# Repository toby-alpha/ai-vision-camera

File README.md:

# ai-vision-camera
A CM5 Based Camera used for Scene Description

**As mentioned in the bottom of this ReadMe, JLCCNC  generously sponsored my project, making it possible for me, as a high school student, to create a professional-grade end product. I would truely recommend that you take a look at the services JLCCNC can provide, the photos really show the quality for itself.**

## What is this?

A Radxa CM5 driven camera, capable of providing detailed scene description by taking in an image through a camera and outputing it as sound, through a speaker,  to a visually impared person by using an on-board AI alogrithm. It's then housed in a 6061 Aluminium Case, providing both elegance but also an efficient method of heat disipation. 

## CAD

## PCB(s)

### Main Radxa CM5 Interface

### WS2812B RGB Halo

### Trigger Button

## Wiring Diagram

## Why I made this?

So.. I really wanted to explore using a local AI alogrithm, that could be effectivly tuned to meet a purpose. Doing reaserch, I really loved the form factor, and power of the CM5, and thus wanted to combine the two together to produce something meaningful. To be meaningful, and fufil a real world purpose, the device takes in an image, then spits out a description through a speaker, to aid a visually impared person. I see this as both being a really effective way to explore and deepen my knowledge in this area, but also create a positive contribution to society. This concept of description can be seen in other solutions, such as Microsoft's SeeingAI. I think my project has been a really meaningful exploration of this technology.

## BOM

|Item                                |Cost AUD|Cost USD|Vendor    |Link                                                |
|------------------------------------|--------|--------|----------|----------------------------------------------------|
|Top Case                            |76      |49.4  |JLCCNC   |https://jlccnc.com/?from=Toby              |
|Bottom Case                         |76      |49.4    |JLCCNC   |https://jlccnc.com/?from=Toby               |
|LED Diffuser                        |20      |13      |JLCCNC   |https://jlccnc.com/?from=Toby               |
|Button                              |15      |9.75    |JLCCNC   |https://jlccnc.com/?from=Toby               |
|                                    |        |        |          |                                                    |
|Radxa CM5                           |137 (Will aquire personally, if this is too much)   |90     |Aliexpress|https://vi.aliexpress.com/item/1005007512045699.html|
|Radxa 8MP Camera                    |30      |19.5    |Aliexpress|https://vi.aliexpress.com/item/1005006991546297.html|
|Hot Air Gun (For the back connector)|46      |29.9    |Aliexpress|https://vi.aliexpress.com/item/1005008042972683.html|
|PCB Components                      |15      |9.75    |Aliexpress|Misc                                                |
|Misc (Bolts, Camera Cable, Speaker, Vibration Motor)          |15      |9.75    |Aliexpress|Misc                                                |
|                                    |        |        |          |                                                    |
|Main PCB                            |10      |6.5     |JLCPCB    |Manual Quote - Please Enquire to View               |
|Main PCBA                           |48      |31.2    |JLCPCB    |Manual Quote - Please Enquire to View               |
|LED Diffuser PCB                    |5       |3.25    |JLCPCB    |Manual Quote - Please Enquire to View               |
|Button PCB                          |5       |3.25    |JLCPCB    |Manual Quote - Please Enquire to View               |
|                                    |        |        |          |                                                    |
|Total                               |477     |311   |          |                                                    |

---

### A HUGE thank you so JLCCNC for sponsoring the CNC part of this project. Their assistance in machining will be crucial in helping this project come to life. 

If you are looking for CNC services, I can not reccomend them more. https://jlccnc.com/?from=Toby

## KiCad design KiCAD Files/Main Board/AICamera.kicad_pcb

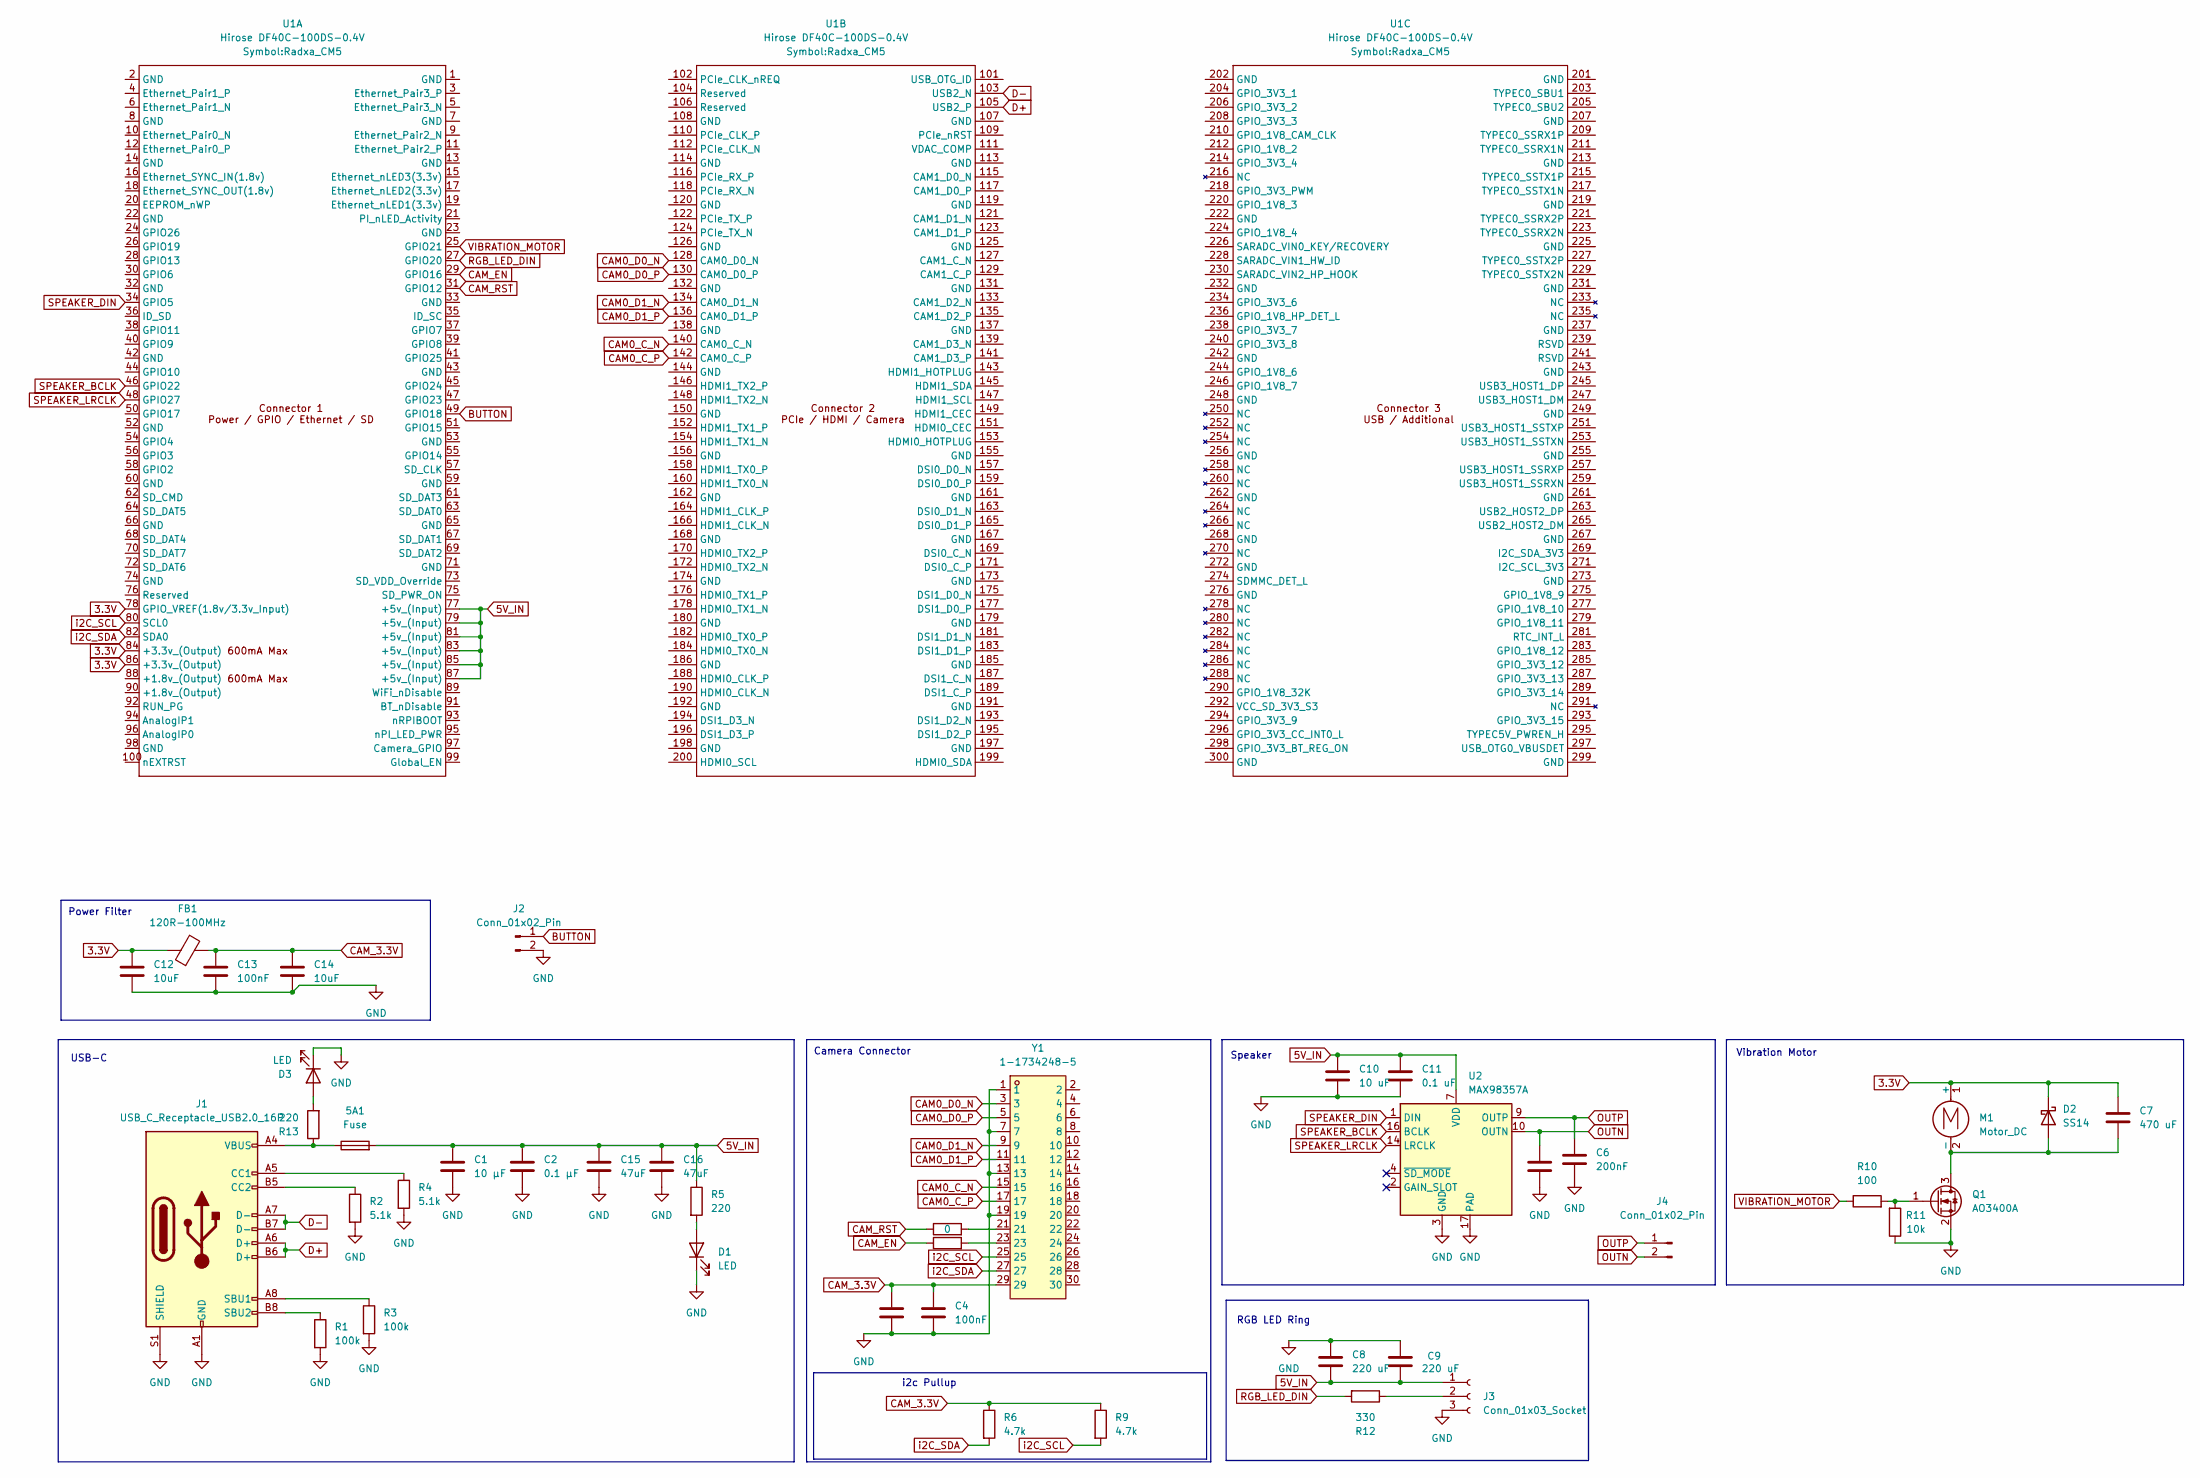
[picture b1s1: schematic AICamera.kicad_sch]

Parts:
5A1: Fuse; Fuse_1206_3216Metric
C1: 10 µF; C_0805_2012Metric
C2: 0.1 µF; C_0805_2012Metric
C3, C12, C14: 10uF; C_0805_2012Metric
C4, C13: 100nF; C_0805_2012Metric
C5, C6: 200nF; C_0805_2012Metric
C7: 470 uF; C_0805_2012Metric
C8, C9: 220 uF; C_0805_2012Metric
C10: 10 uF; C_0805_2012Metric
C11: 0.1 uF; C_0805_2012Metric
C15, C16: 47uF; C_1206_3216Metric
D1, D3: LED; LED_0805_2012Metric
D2: SS14; D_SMA
FB1: 120R-100MHz; C_0805_2012Metric
J1: USB_C_Receptacle_USB2.0_16P; USB_C_Receptacle_G-Switch_GT-USB-7010ASV
J2: Conn_01x02_Pin; TestPoint_Pad_3.0x3.0mm
J3: Conn_01x03_Socket; TestPoint_Pad_2.5x2.5mm
J4: Conn_01x02_Pin; TestPoint_Pad_2.0x2.0mm
M1: Motor_DC; TestPoint_Pad_2.0x2.0mm
Q1: AO3400A; SOT-23
R1, R3: 100k; R_0805_2012Metric
R2, R4: 5.1k; R_0805_2012Metric
R5, R13: 220; R_0805_2012Metric
R6, R9: 4.7k; R_0603_1608Metric
R7, R8: 0; R_0805_2012Metric
R10: 100; R_0805_2012Metric
R11: 10k; R_0805_2012Metric
R12: 330; R_0805_2012Metric
U1: Hirose DF40C-100DS-0.4V; Radxa_CM5
U2: MAX98357A; TQFN-16-1EP_3x3mm_P0.5mm_EP1.23x1.23mm
Y1: 1-1734248-5; CONN-SMD_1-1734248-5; LCSC Part C2922285

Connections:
3.3V: C7.2, C12.1, D2.1 (K), FB1.1, M1.1 (+), U1.78 (GPIO_VREF(1.8v/3.3v_Input)), U1.84 (+3.3v_(Output)), U1.86 (+3.3v_(Output))
5V_IN: 5A1.2, C1.1, C2.1, C8.2, C9.2, C10.1, C11.1, C15.1, C16.1, J3.1, R5.1, U1.77 (+5v_(Input)), U1.79 (+5v_(Input)), U1.81 (+5v_(Input)), U1.83 (+5v_(Input)), U1.85 (+5v_(Input)), U1.87 (+5v_(Input)), U2.7 (VDD), U2.8 (VDD)
BUTTON: J2.1, U1.49 (GPIO18)
CAM0_C_N: U1.140 (CAM0_C_N), Y1.15
CAM0_C_P: U1.142 (CAM0_C_P), Y1.17
CAM0_D0_N: U1.128 (CAM0_D0_N), Y1.3
CAM0_D0_P: U1.130 (CAM0_D0_P), Y1.5
CAM0_D1_N: U1.134 (CAM0_D1_N), Y1.9
CAM0_D1_P: U1.136 (CAM0_D1_P), Y1.11
CAM_3.3V: C3.1, C4.1, C13.1, C14.1, FB1.2, R6.1, R9.1, Y1.29
CAM_EN: R8.1, U1.29 (GPIO16)
CAM_RST: R7.1, U1.31 (GPIO12)
D+: J1.A6 (D+), J1.B6 (D+), U1.105 (USB2_P)
D-: J1.A7 (D-), J1.B7 (D-), U1.103 (USB2_N)
GND: C1.2, C2.2, C3.2, C4.2, C5.2, C6.2, C8.1, C9.1, C10.2, C11.2, C12.2, C13.2, C14.2, C15.2, C16.2, D1.1 (K), D3.1 (K), J1.A1 (GND), J1.A12 (GND), J1.B1 (GND), J1.B12 (GND), J1.S1 (SHIELD), J2.2, J3.3, Q1.2 (S), R1.2, R2.2, R3.2, R4.2, R11.1, U2.3 (GND), U2.11 (GND), U2.15 (GND), U2.17 (PAD), Y1.1, Y1.7, Y1.13, Y1.19
unnamed: 5A1.1, J1.A4 (VBUS), J1.A9 (VBUS), J1.B4 (VBUS), J1.B9 (VBUS), R13.1
unnamed: D1.2 (A), R5.2
unnamed: C7.1, D2.2 (A), M1.2 (-), Q1.3 (D)
unnamed: D3.2 (A), R13.2
unnamed: J1.A5 (CC1), R4.1
unnamed: J1.B5 (CC2), R2.1
unnamed: J1.A8 (SBU1), R3.1
unnamed: J1.B8 (SBU2), R1.1
unnamed: J3.2, R12.1
unnamed: Q1.1 (G), R10.2, R11.2
unnamed: R7.2, Y1.21
unnamed: R8.2, Y1.23
OUTN: C5.1, J4.2, U2.10 (OUTN)
OUTP: C6.1, J4.1, U2.9 (OUTP)
RGB_LED_DIN: R12.2, U1.27 (GPIO20)
SPEAKER_BCLK: U1.46 (GPIO22), U2.16 (BCLK)
SPEAKER_DIN: U1.34 (GPIO5), U2.1 (DIN)
SPEAKER_LRCLK: U1.48 (GPIO27), U2.14 (LRCLK)
VIBRATION_MOTOR: R10.1, U1.25 (GPIO21)
i2C_SCL: R9.2, U1.80 (SCL0), Y1.25
i2C_SDA: R6.2, U1.82 (SDA0), Y1.27

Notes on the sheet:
i2c Pullup
Speaker
USB-C
RGB LED Ring
Power Filter
Camera Connector
Vibration Motor

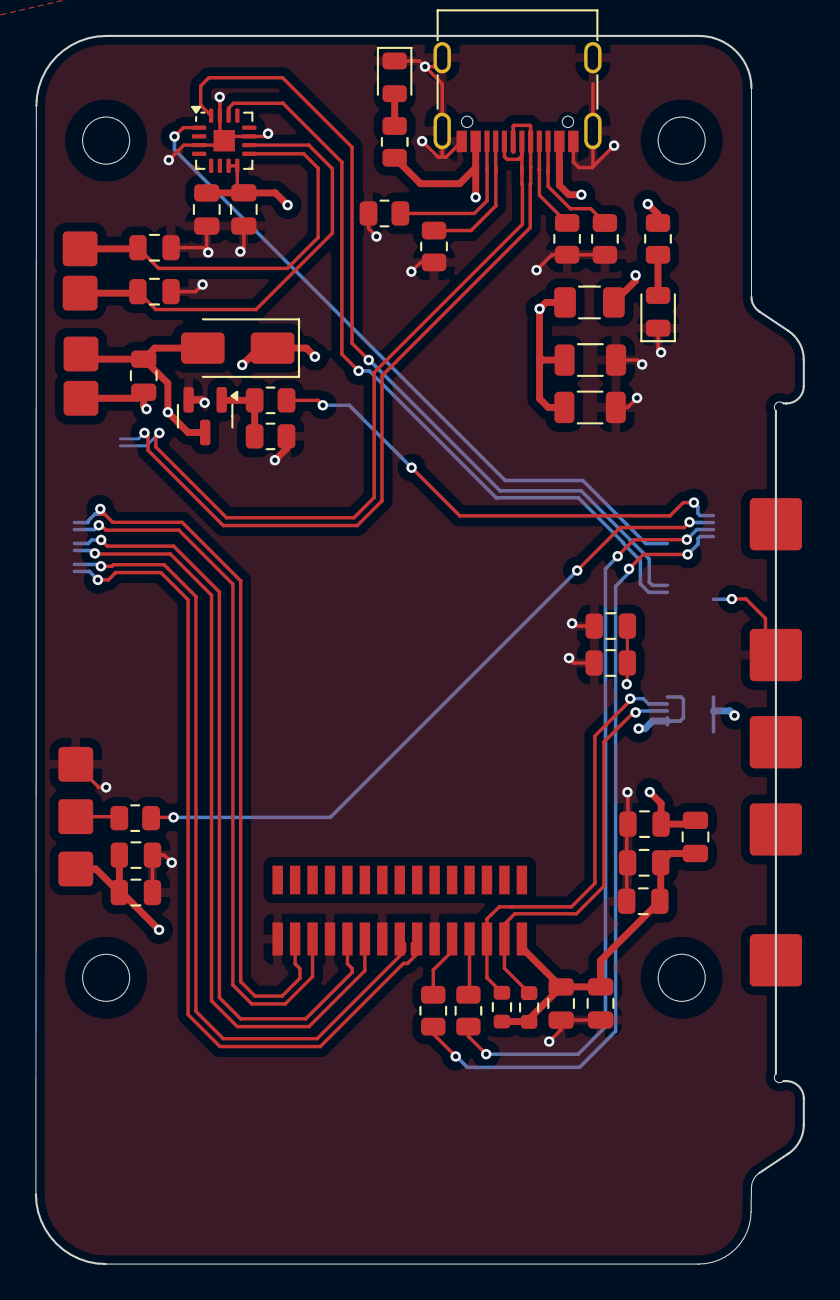
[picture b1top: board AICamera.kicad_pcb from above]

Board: 4 copper layers, 44.0 x 70.4 mm, 43 parts (1 on the bottom side), 36 nets.

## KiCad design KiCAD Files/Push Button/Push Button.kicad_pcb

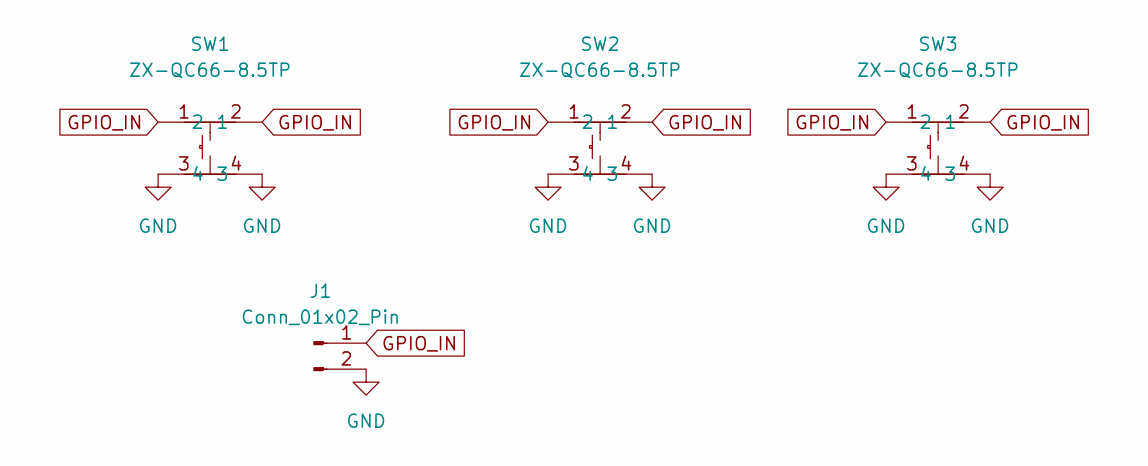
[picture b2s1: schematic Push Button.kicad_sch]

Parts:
J1: Conn_01x02_Pin; TestPoint_Pad_3.0x3.0mm
SW1, SW2, SW3: ZX-QC66-8.5TP; KEY-SMD_4P-L6.0-W6.0-P4.50-LS8.6_H8.5; LCSC Part C7470159

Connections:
GND: J1.2, SW1.3, SW1.4, SW2.3, SW2.4, SW3.3, SW3.4
GPIO_IN: J1.1, SW1.1, SW1.2, SW2.1, SW2.2, SW3.1, SW3.2

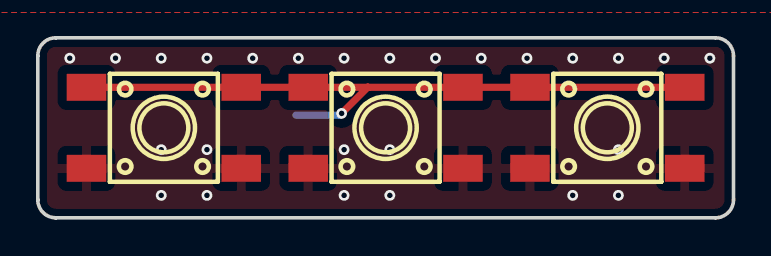
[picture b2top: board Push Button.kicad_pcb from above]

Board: 2 copper layers, 38.7 x 10.0 mm, 4 parts (1 on the bottom side), 2 nets.

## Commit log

2025-07-16 CAD (Check Message)
    Unfortunately, the file is too big with the PCB's included, send me a message if you'd like the full CAD and I'll happily send it over!!
2025-07-17 added files
2025-07-17 Added CAD (Check Message)
    Does not include PCB, please message me if you want the full model.
2025-07-17 Added FULL CAD
